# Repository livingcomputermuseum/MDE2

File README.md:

# MDE2 - MASSBUS Disk Emulator

This repository contains the Xilinx VHDL code and PCB designs for the MASSBUS Disk Emulator.

This is used in tandem with the MBS server code to emulate MASSBUS peripherals.

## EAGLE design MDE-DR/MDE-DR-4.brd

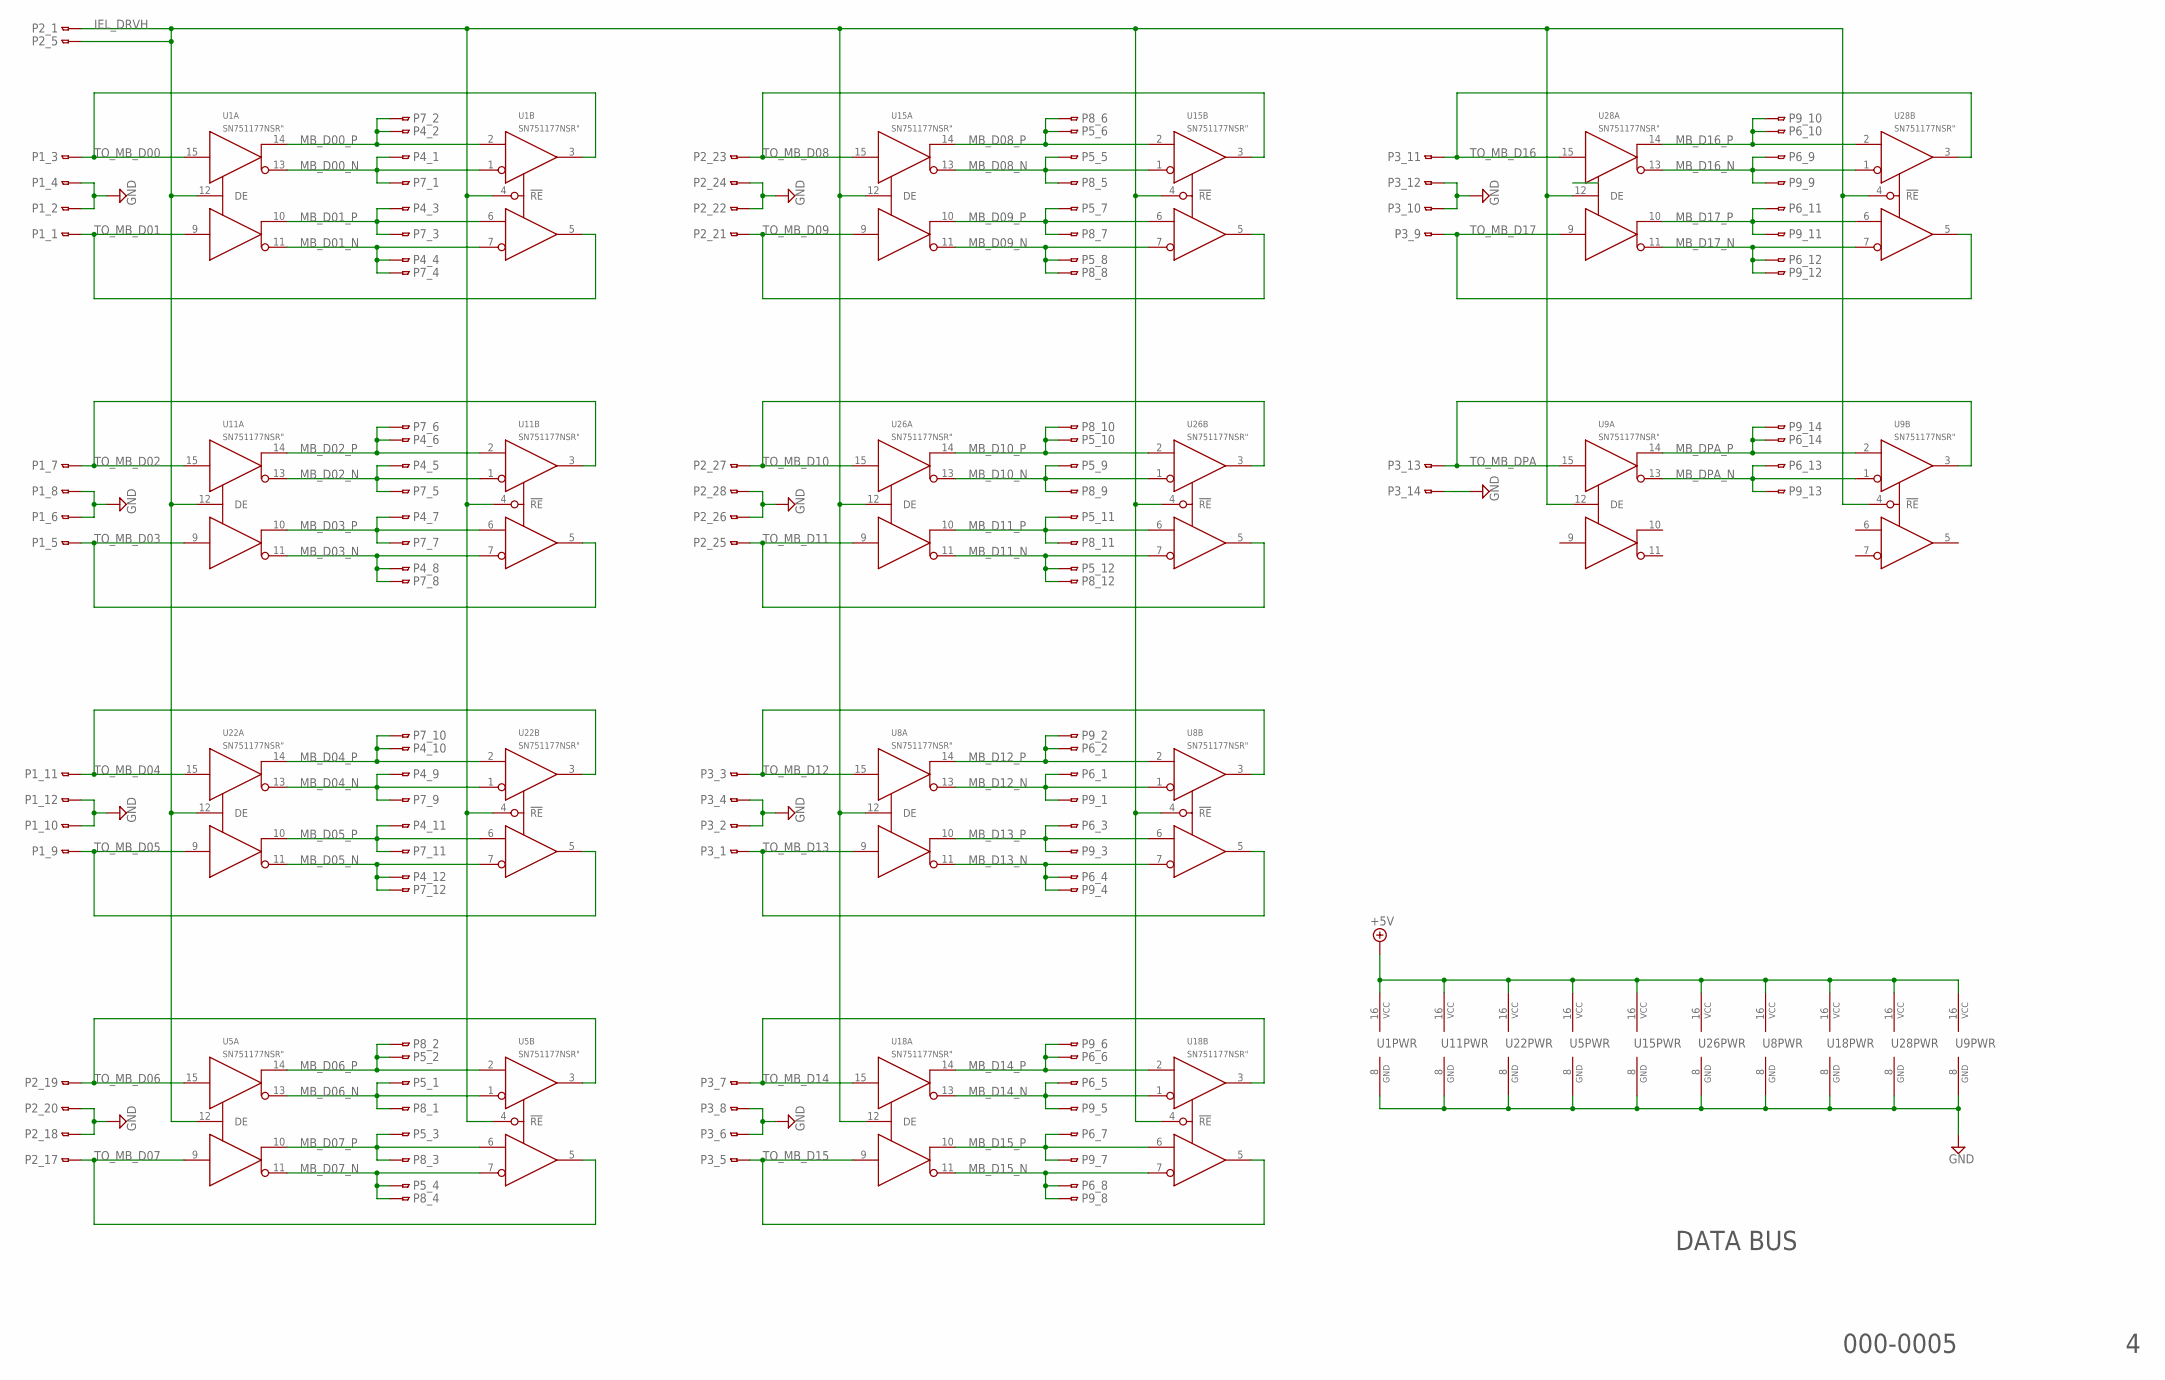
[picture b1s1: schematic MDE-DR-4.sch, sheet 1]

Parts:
P1, P2, P3: CON50L
P4, P5, P6, P7, P8, P9: CON40L
U1, U5, U8, U9, U11, U15, U18, U22, U26, U28: SN751177NSR"; SO16NS

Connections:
+5V: U1.16 (VCC), U5.16 (VCC), U8.16 (VCC), U9.16 (VCC), U11.16 (VCC), U15.16 (VCC), U18.16 (VCC), U22.16 (VCC), U26.16 (VCC), U28.16 (VCC); also elsewhere on the board
GND: P1.2, P1.4, P1.6, P1.8, P1.10, P1.12, P2.18, P2.20, P2.22, P2.24, P2.26, P2.28, P3.2, P3.4, P3.6, P3.8, P3.10, P3.12, P3.14, U1.8 (GND), U5.8 (GND), U8.8 (GND), U9.8 (GND), U11.8 (GND), U15.8 (GND), U18.8 (GND), U22.8 (GND), U26.8 (GND), U28.8 (GND); also elsewhere on the board
IEL_DRVH: P2.1, P2.5, U1.4 (!RE), U1.12 (DE), U5.4 (!RE), U5.12 (DE), U8.4 (!RE), U8.12 (DE), U9.4 (!RE), U9.12 (DE), U11.4 (!RE), U11.12 (DE), U15.4 (!RE), U15.12 (DE), U18.4 (!RE), U18.12 (DE), U22.4 (!RE), U22.12 (DE), U26.4 (!RE), U26.12 (DE), U28.4 (!RE), U28.12 (DE)
MB_D00_N: P4.1, P7.1, U1.1 (!1B), U1.13 (!1Z)
MB_D00_P: P4.2, P7.2, U1.2 (1A), U1.14 (1Y)
MB_D01_N: P4.4, P7.4, U1.7 (!2B), U1.11 (!2Z)
MB_D01_P: P4.3, P7.3, U1.6 (2A), U1.10 (2Y)
MB_D02_N: P4.5, P7.5, U11.1 (!1B), U11.13 (!1Z)
MB_D02_P: P4.6, P7.6, U11.2 (1A), U11.14 (1Y)
MB_D03_N: P4.8, P7.8, U11.7 (!2B), U11.11 (!2Z)
MB_D03_P: P4.7, P7.7, U11.6 (2A), U11.10 (2Y)
MB_D04_N: P4.9, P7.9, U22.1 (!1B), U22.13 (!1Z)
MB_D04_P: P4.10, P7.10, U22.2 (1A), U22.14 (1Y)
MB_D05_N: P4.12, P7.12, U22.7 (!2B), U22.11 (!2Z)
MB_D05_P: P4.11, P7.11, U22.6 (2A), U22.10 (2Y)
MB_D06_N: P5.1, P8.1, U5.1 (!1B), U5.13 (!1Z)
MB_D06_P: P5.2, P8.2, U5.2 (1A), U5.14 (1Y)
MB_D07_N: P5.4, P8.4, U5.7 (!2B), U5.11 (!2Z)
MB_D07_P: P5.3, P8.3, U5.6 (2A), U5.10 (2Y)
MB_D08_N: P5.5, P8.5, U15.1 (!1B), U15.13 (!1Z)
MB_D08_P: P5.6, P8.6, U15.2 (1A), U15.14 (1Y)
MB_D09_N: P5.8, P8.8, U15.7 (!2B), U15.11 (!2Z)
MB_D09_P: P5.7, P8.7, U15.6 (2A), U15.10 (2Y)
MB_D10_N: P5.9, P8.9, U26.1 (!1B), U26.13 (!1Z)
MB_D10_P: P5.10, P8.10, U26.2 (1A), U26.14 (1Y)
MB_D11_N: P5.12, P8.12, U26.7 (!2B), U26.11 (!2Z)
MB_D11_P: P5.11, P8.11, U26.6 (2A), U26.10 (2Y)
MB_D12_N: P6.1, P9.1, U8.1 (!1B), U8.13 (!1Z)
MB_D12_P: P6.2, P9.2, U8.2 (1A), U8.14 (1Y)
MB_D13_N: P6.4, P9.4, U8.7 (!2B), U8.11 (!2Z)
MB_D13_P: P6.3, P9.3, U8.6 (2A), U8.10 (2Y)
MB_D14_N: P6.5, P9.5, U18.1 (!1B), U18.13 (!1Z)
MB_D14_P: P6.6, P9.6, U18.2 (1A), U18.14 (1Y)
MB_D15_N: P6.8, P9.8, U18.7 (!2B), U18.11 (!2Z)
MB_D15_P: P6.7, P9.7, U18.6 (2A), U18.10 (2Y)
MB_D16_N: P6.9, P9.9, U28.1 (!1B), U28.13 (!1Z)
MB_D16_P: P6.10, P9.10, U28.2 (1A), U28.14 (1Y)
MB_D17_N: P6.12, P9.12, U28.7 (!2B), U28.11 (!2Z)
MB_D17_P: P6.11, P9.11, U28.6 (2A), U28.10 (2Y)
MB_DPA_N: P6.13, P9.13, U9.1 (!1B), U9.13 (!1Z)
MB_DPA_P: P6.14, P9.14, U9.2 (1A), U9.14 (1Y)
TO_MB_D00: P1.3, U1.3 (1R), U1.15 (1D)
TO_MB_D01: P1.1, U1.5 (2R), U1.9 (2D)
TO_MB_D02: P1.7, U11.3 (1R), U11.15 (1D)
TO_MB_D03: P1.5, U11.5 (2R), U11.9 (2D)
TO_MB_D04: P1.11, U22.3 (1R), U22.15 (1D)
TO_MB_D05: P1.9, U22.5 (2R), U22.9 (2D)
TO_MB_D06: P2.19, U5.3 (1R), U5.15 (1D)
TO_MB_D07: P2.17, U5.5 (2R), U5.9 (2D)
TO_MB_D08: P2.23, U15.3 (1R), U15.15 (1D)
TO_MB_D09: P2.21, U15.5 (2R), U15.9 (2D)
TO_MB_D10: P2.27, U26.3 (1R), U26.15 (1D)
TO_MB_D11: P2.25, U26.5 (2R), U26.9 (2D)
TO_MB_D12: P3.3, U8.3 (1R), U8.15 (1D)
TO_MB_D13: P3.1, U8.5 (2R), U8.9 (2D)
TO_MB_D14: P3.7, U18.3 (1R), U18.15 (1D)
TO_MB_D15: P3.5, U18.5 (2R), U18.9 (2D)
TO_MB_D16: P3.11, U28.3 (1R), U28.15 (1D)
TO_MB_D17: P3.9, U28.5 (2R), U28.9 (2D)
TO_MB_DPA: P3.13, U9.3 (1R), U9.15 (1D)

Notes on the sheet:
DATA BUS
000-0005

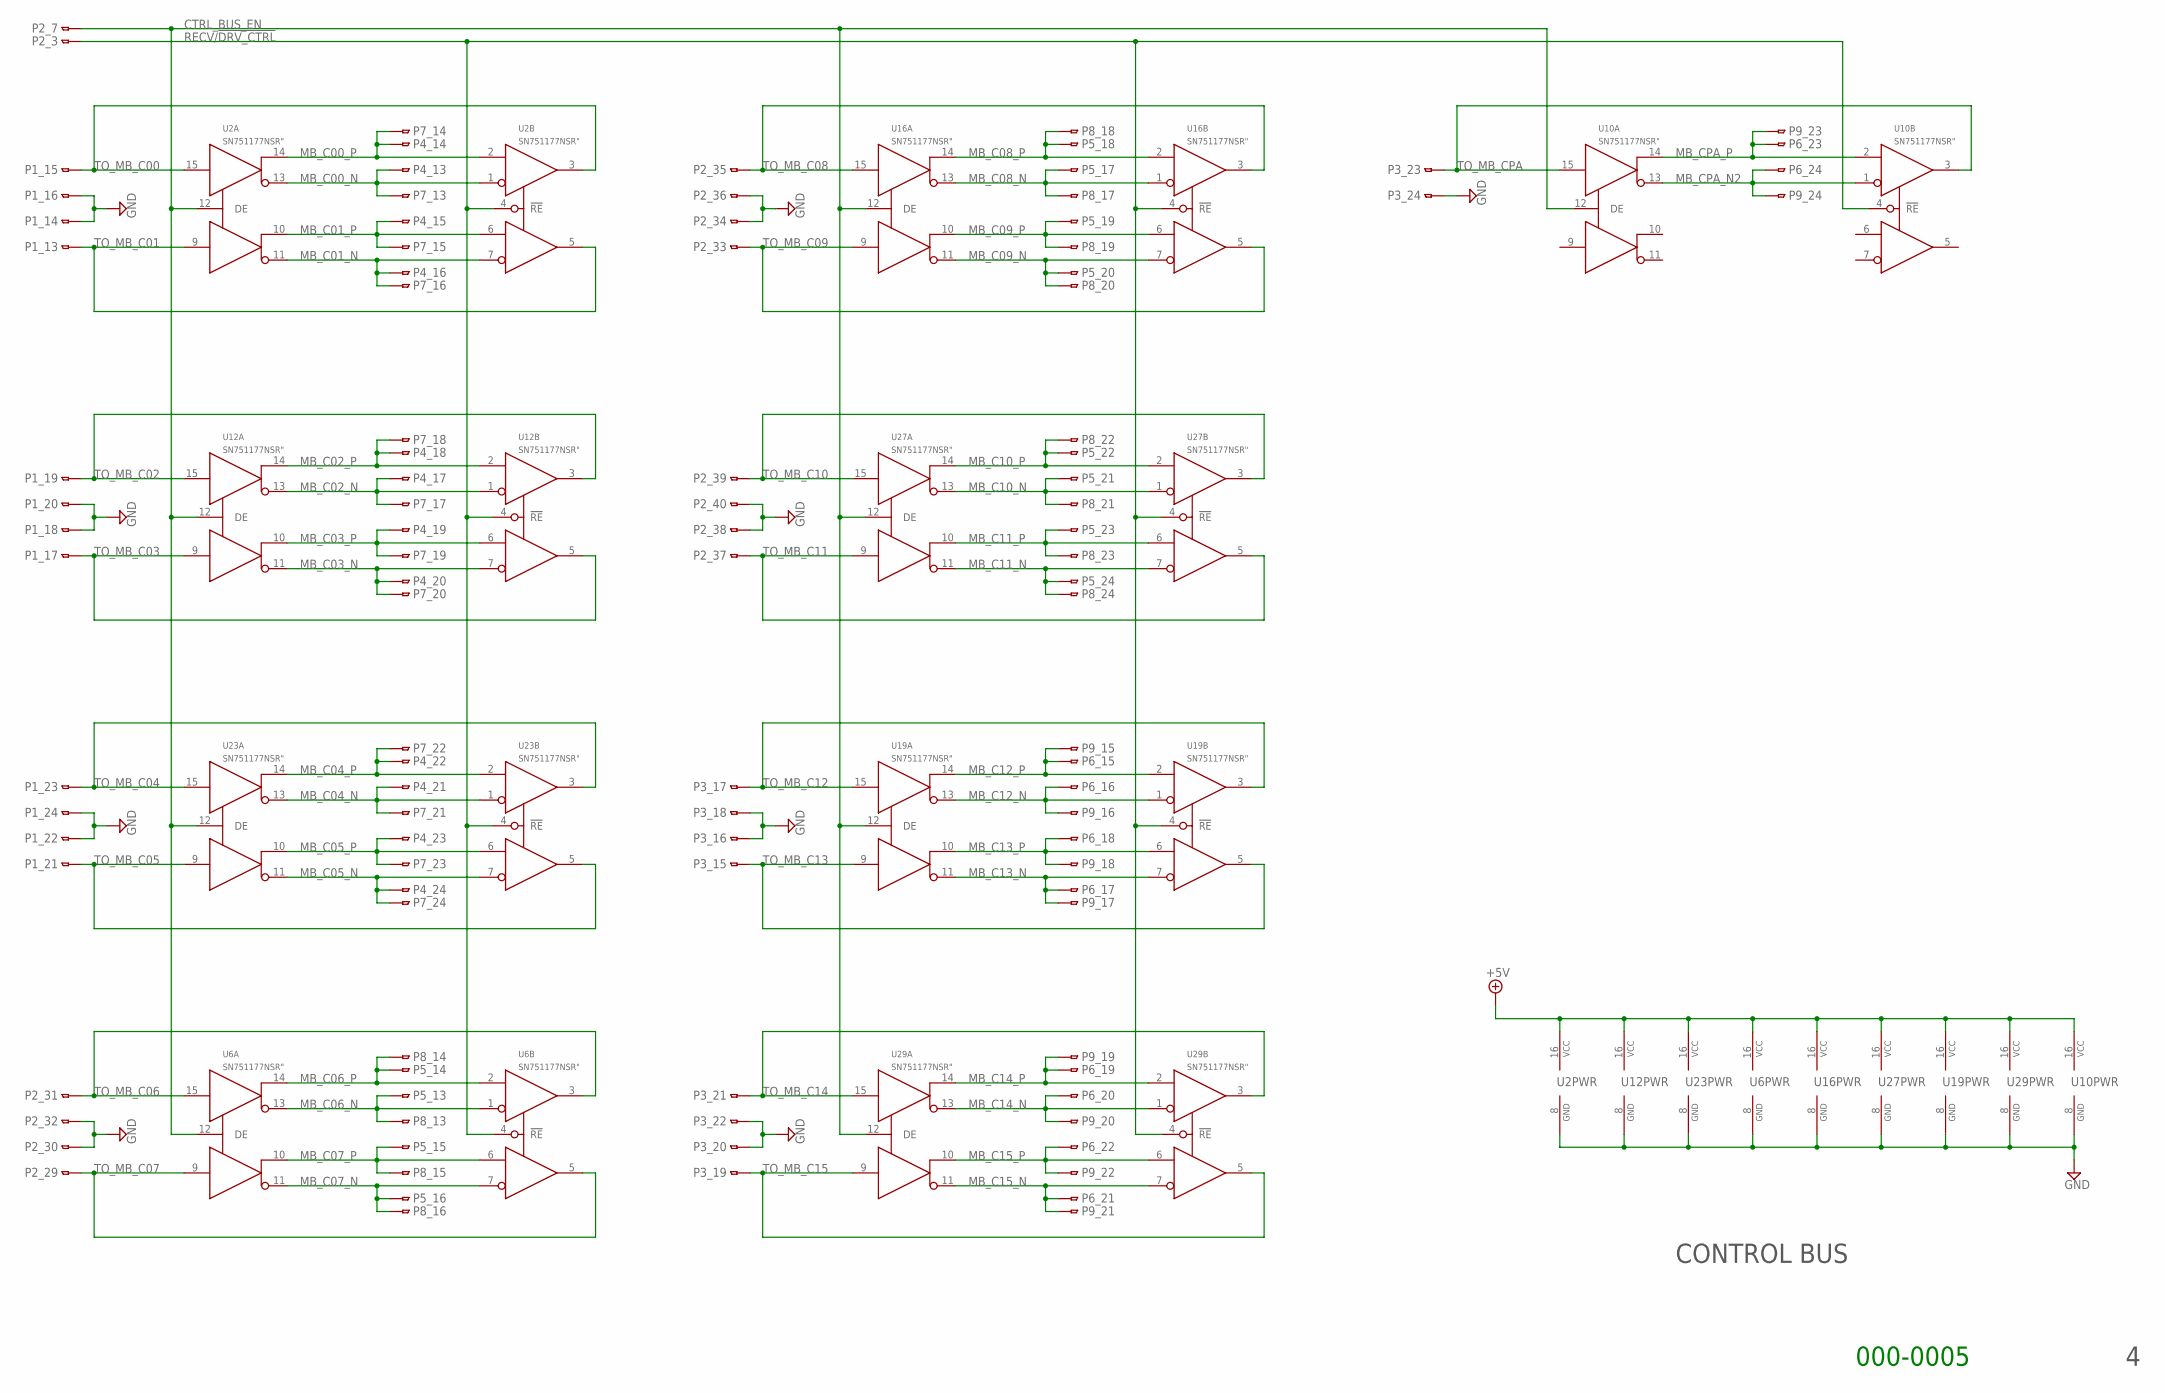
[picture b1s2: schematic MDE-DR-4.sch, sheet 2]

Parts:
P1, P2, P3: CON50L
P4, P5, P6, P7, P8, P9: CON40L
U2, U6, U10, U12, U16, U19, U23, U27, U29: SN751177NSR"; SO16NS

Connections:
+5V: U2.16 (VCC), U6.16 (VCC), U10.16 (VCC), U12.16 (VCC), U16.16 (VCC), U19.16 (VCC), U23.16 (VCC), U27.16 (VCC), U29.16 (VCC); also elsewhere on the board
CTRL_BUS_EN: P2.7, U2.12 (DE), U6.12 (DE), U10.12 (DE), U12.12 (DE), U16.12 (DE), U19.12 (DE), U23.12 (DE), U27.12 (DE), U29.12 (DE)
GND: P1.14, P1.16, P1.18, P1.20, P1.22, P1.24, P2.30, P2.32, P2.34, P2.36, P2.38, P2.40, P3.16, P3.18, P3.20, P3.22, P3.24, U2.8 (GND), U6.8 (GND), U10.8 (GND), U12.8 (GND), U16.8 (GND), U19.8 (GND), U23.8 (GND), U27.8 (GND), U29.8 (GND); also elsewhere on the board
MB_C00_N: P4.13, P7.13, U2.1 (!1B), U2.13 (!1Z)
MB_C00_P: P4.14, P7.14, U2.2 (1A), U2.14 (1Y)
MB_C01_N: P4.16, P7.16, U2.7 (!2B), U2.11 (!2Z)
MB_C01_P: P4.15, P7.15, U2.6 (2A), U2.10 (2Y)
MB_C02_N: P4.17, P7.17, U12.1 (!1B), U12.13 (!1Z)
MB_C02_P: P4.18, P7.18, U12.2 (1A), U12.14 (1Y)
MB_C03_N: P4.20, P7.20, U12.7 (!2B), U12.11 (!2Z)
MB_C03_P: P4.19, P7.19, U12.6 (2A), U12.10 (2Y)
MB_C04_N: P4.21, P7.21, U23.1 (!1B), U23.13 (!1Z)
MB_C04_P: P4.22, P7.22, U23.2 (1A), U23.14 (1Y)
MB_C05_N: P4.24, P7.24, U23.7 (!2B), U23.11 (!2Z)
MB_C05_P: P4.23, P7.23, U23.6 (2A), U23.10 (2Y)
MB_C06_N: P5.13, P8.13, U6.1 (!1B), U6.13 (!1Z)
MB_C06_P: P5.14, P8.14, U6.2 (1A), U6.14 (1Y)
MB_C07_N: P5.16, P8.16, U6.7 (!2B), U6.11 (!2Z)
MB_C07_P: P5.15, P8.15, U6.6 (2A), U6.10 (2Y)
MB_C08_N: P5.17, P8.17, U16.1 (!1B), U16.13 (!1Z)
MB_C08_P: P5.18, P8.18, U16.2 (1A), U16.14 (1Y)
MB_C09_N: P5.20, P8.20, U16.7 (!2B), U16.11 (!2Z)
MB_C09_P: P5.19, P8.19, U16.6 (2A), U16.10 (2Y)
MB_C10_N: P5.21, P8.21, U27.1 (!1B), U27.13 (!1Z)
MB_C10_P: P5.22, P8.22, U27.2 (1A), U27.14 (1Y)
MB_C11_N: P5.24, P8.24, U27.7 (!2B), U27.11 (!2Z)
MB_C11_P: P5.23, P8.23, U27.6 (2A), U27.10 (2Y)
MB_C12_N: P6.16, P9.16, U19.1 (!1B), U19.13 (!1Z)
MB_C12_P: P6.15, P9.15, U19.2 (1A), U19.14 (1Y)
MB_C13_N: P6.17, P9.17, U19.7 (!2B), U19.11 (!2Z)
MB_C13_P: P6.18, P9.18, U19.6 (2A), U19.10 (2Y)
MB_C14_N: P6.20, P9.20, U29.1 (!1B), U29.13 (!1Z)
MB_C14_P: P6.19, P9.19, U29.2 (1A), U29.14 (1Y)
MB_C15_N: P6.21, P9.21, U29.7 (!2B), U29.11 (!2Z)
MB_C15_P: P6.22, P9.22, U29.6 (2A), U29.10 (2Y)
MB_CPA_N2: P6.24, P9.24, U10.1 (!1B), U10.13 (!1Z)
MB_CPA_P: P6.23, P9.23, U10.2 (1A), U10.14 (1Y)
RECV/!DRV_CTRL: P2.3, U2.4 (!RE), U6.4 (!RE), U10.4 (!RE), U12.4 (!RE), U16.4 (!RE), U19.4 (!RE), U23.4 (!RE), U27.4 (!RE), U29.4 (!RE)
TO_MB_C00: P1.15, U2.3 (1R), U2.15 (1D)
TO_MB_C01: P1.13, U2.5 (2R), U2.9 (2D)
TO_MB_C02: P1.19, U12.3 (1R), U12.15 (1D)
TO_MB_C03: P1.17, U12.5 (2R), U12.9 (2D)
TO_MB_C04: P1.23, U23.3 (1R), U23.15 (1D)
TO_MB_C05: P1.21, U23.5 (2R), U23.9 (2D)
TO_MB_C06: P2.31, U6.3 (1R), U6.15 (1D)
TO_MB_C07: P2.29, U6.5 (2R), U6.9 (2D)
TO_MB_C08: P2.35, U16.3 (1R), U16.15 (1D)
TO_MB_C09: P2.33, U16.5 (2R), U16.9 (2D)
TO_MB_C10: P2.39, U27.3 (1R), U27.15 (1D)
TO_MB_C11: P2.37, U27.5 (2R), U27.9 (2D)
TO_MB_C12: P3.17, U19.3 (1R), U19.15 (1D)
TO_MB_C13: P3.15, U19.5 (2R), U19.9 (2D)
TO_MB_C14: P3.21, U29.3 (1R), U29.15 (1D)
TO_MB_C15: P3.19, U29.5 (2R), U29.9 (2D)
TO_MB_CPA: P3.23, U10.3 (1R), U10.15 (1D)

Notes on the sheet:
CONTROL BUS
000-0005

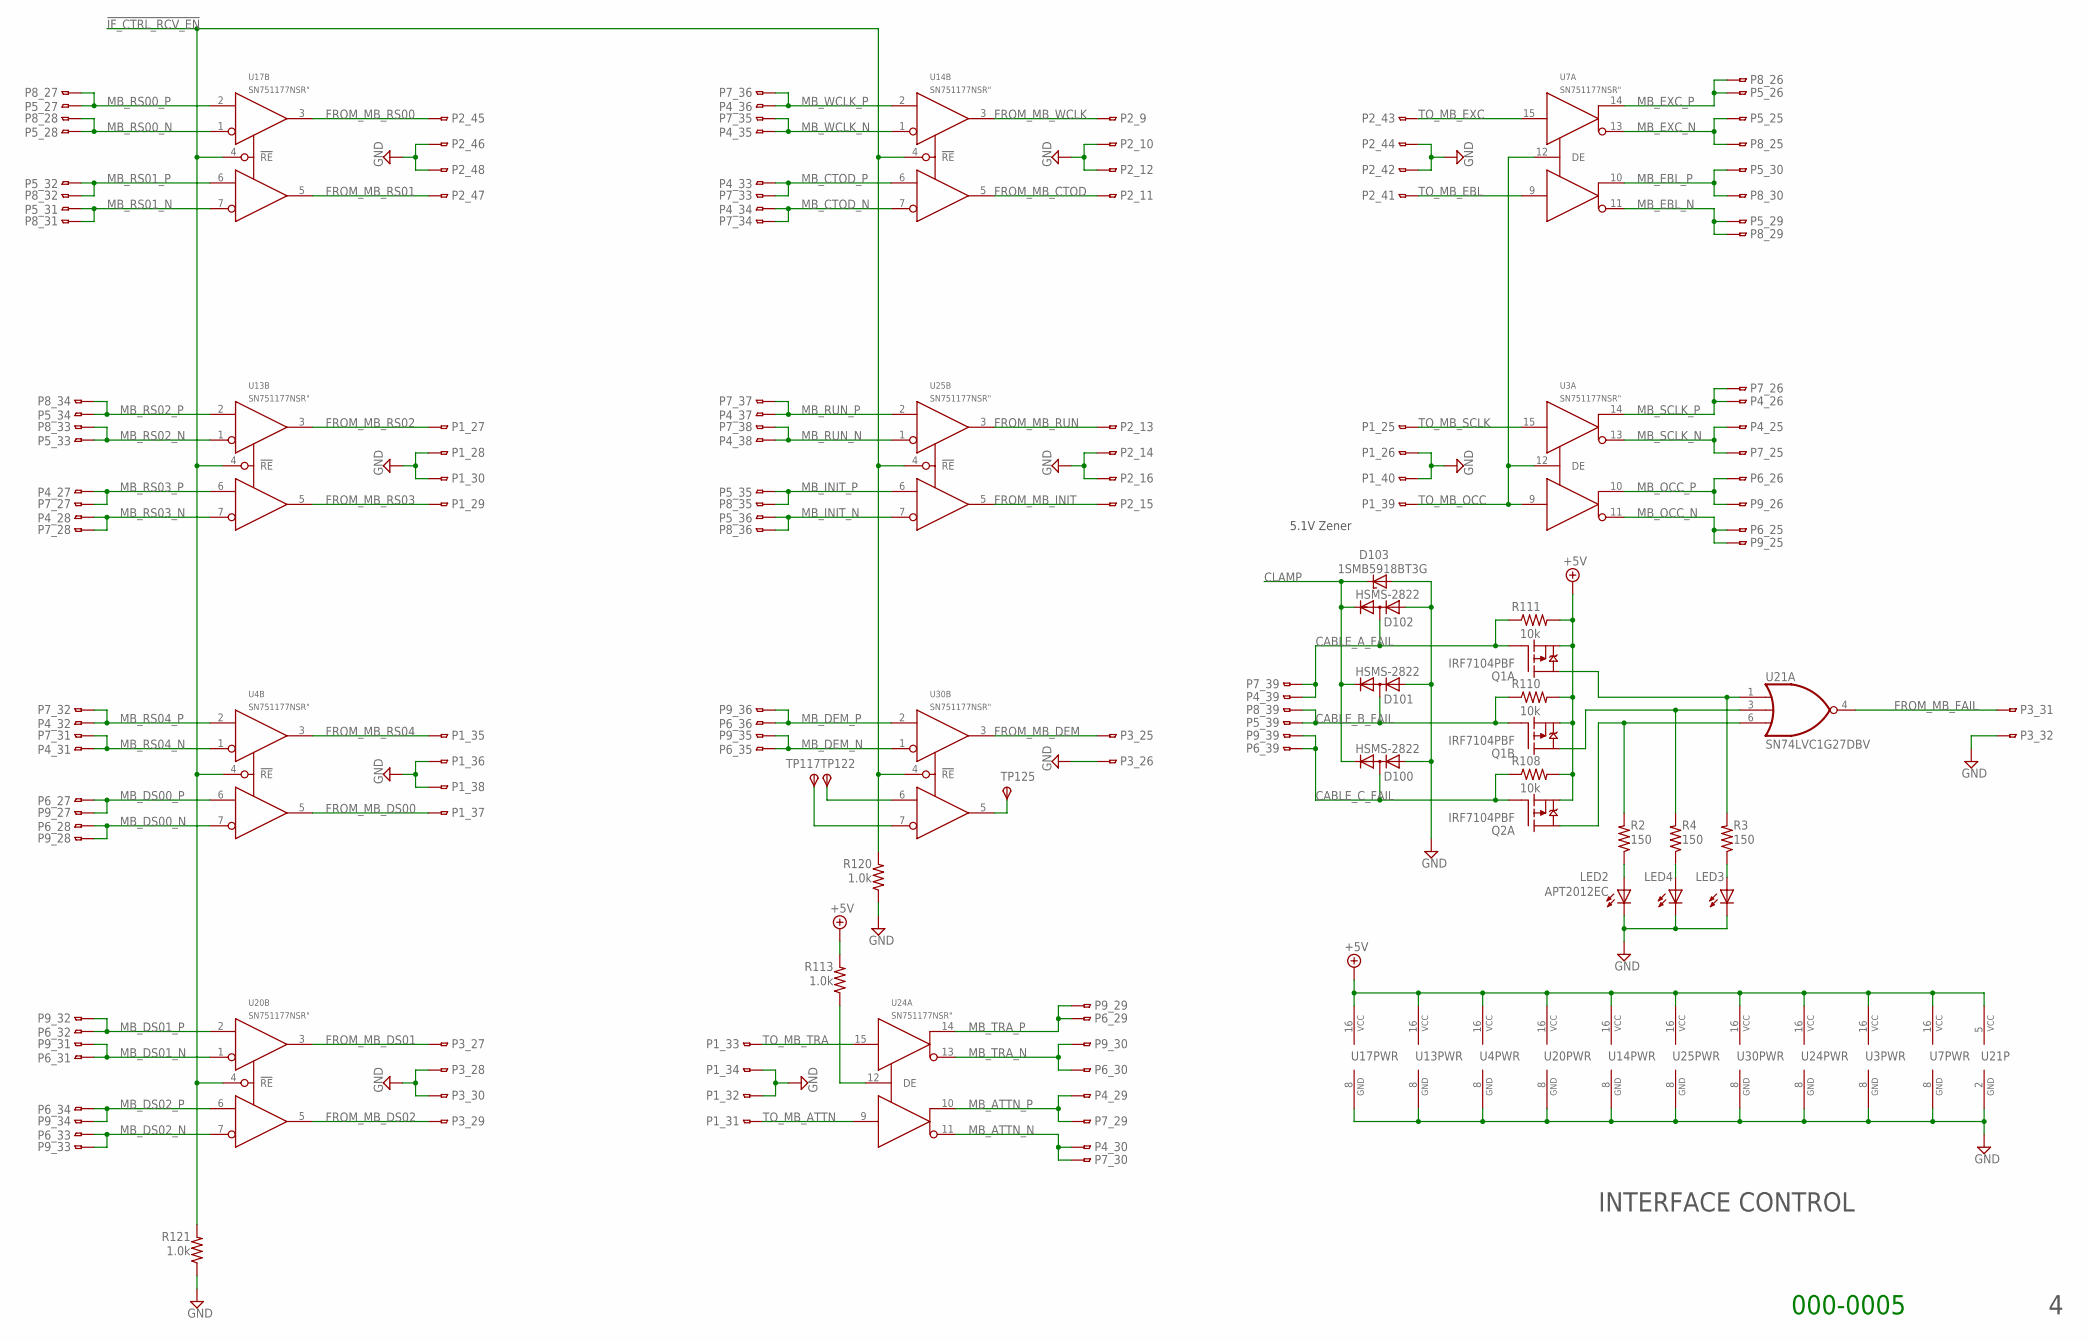
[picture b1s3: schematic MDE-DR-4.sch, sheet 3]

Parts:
D100, D101, D102: HSMS-2822; SOT23
D103: 1SMB5918BT3G; SMB
LED2, LED3, LED4: APT2012EC; SML0805
P1, P2, P3: CON50L
P4, P5, P6, P7, P8, P9: CON40L
Q1, Q2: IRF7104PBF; SO-08
R2, R3, R4: 150; R0805
R108, R110, R111: 10k; R0805
R113, R120, R121: 1.0k; R0805
TP117, TP122, TP125: TPSTP12R; TP12R
U3, U4, U7, U13, U14, U17, U20, U24, U25, U30: SN751177NSR"; SO16NS
U21: SN74LVC1G27DBV; DBV_R-PDSO-G6

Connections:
!IF_CTRL_RCV_EN: R120.2, R121.2, U4.4 (!RE), U13.4 (!RE), U14.4 (!RE), U17.4 (!RE), U20.4 (!RE), U25.4 (!RE), U30.4 (!RE)
+5V: Q1.1 (S), Q1.3 (S), Q2.1 (S), R108.2, R110.2, R111.2, R113.2, U3.16 (VCC), U4.16 (VCC), U7.16 (VCC), U13.16 (VCC), U14.16 (VCC), U17.16 (VCC), U20.16 (VCC), U21.5 (VCC), U24.16 (VCC), U25.16 (VCC), U30.16 (VCC); also elsewhere on the board
CABLE_A_FAIL: D102.3 (AC), P4.39, P7.39, Q1.2 (G), R111.1
CABLE_B_FAIL: D101.3 (AC), P5.39, P8.39, Q1.4 (G), R110.1
CABLE_C_FAIL: D100.3 (AC), P6.39, P9.39, Q2.2 (G), R108.1
CLAMP: D100.2 (C), D101.2 (C), D102.2 (C), D103.C
FROM_MB_CTOD: P2.11, U14.5 (2R)
FROM_MB_DEM: P3.25, U30.3 (1R)
FROM_MB_DS00: P1.37, U4.5 (2R)
FROM_MB_DS01: P3.27, U20.3 (1R)
FROM_MB_DS02: P3.29, U20.5 (2R)
FROM_MB_FAIL: P3.31, U21.4 (Y)
FROM_MB_INIT: P2.15, U25.5 (2R)
FROM_MB_RS00: P2.45, U17.3 (1R)
FROM_MB_RS01: P2.47, U17.5 (2R)
FROM_MB_RS02: P1.27, U13.3 (1R)
FROM_MB_RS03: P1.29, U13.5 (2R)
FROM_MB_RS04: P1.35, U4.3 (1R)
FROM_MB_RUN: P2.13, U25.3 (1R)
FROM_MB_WCLK: P2.9, U14.3 (1R)
GND: D100.1 (A), D101.1 (A), D102.1 (A), D103.A, LED2.C, LED3.C, LED4.C, P1.26, P1.28, P1.30, P1.32, P1.34, P1.36, P1.38, P1.40, P2.10, P2.12, P2.14, P2.16, P2.42, P2.44, P2.46, P2.48, P3.26, P3.28, P3.30, P3.32, R120.1, R121.1, U3.8 (GND), U4.8 (GND), U7.8 (GND), U13.8 (GND), U14.8 (GND), U17.8 (GND), U20.8 (GND), U21.2 (GND), U24.8 (GND), U25.8 (GND), U30.8 (GND); also elsewhere on the board
MB_ATTN_N: P4.30, P7.30, U24.11 (!2Z)
MB_ATTN_P: P4.29, P7.29, U24.10 (2Y)
MB_CTOD_N: P4.34, P7.34, U14.7 (!2B)
MB_CTOD_P: P4.33, P7.33, U14.6 (2A)
MB_DEM_N: P6.35, P9.35, U30.1 (!1B)
MB_DEM_P: P6.36, P9.36, U30.2 (1A)
MB_DS00_N: P6.28, P9.28, U4.7 (!2B)
MB_DS00_P: P6.27, P9.27, U4.6 (2A)
MB_DS01_N: P6.31, P9.31, U20.1 (!1B)
MB_DS01_P: P6.32, P9.32, U20.2 (1A)
MB_DS02_N: P6.33, P9.33, U20.7 (!2B)
MB_DS02_P: P6.34, P9.34, U20.6 (2A)
MB_EBL_N: P5.29, P8.29, U7.11 (!2Z)
MB_EBL_P: P5.30, P8.30, U7.10 (2Y)
MB_EXC_N: P5.25, P8.25, U7.13 (!1Z)
MB_EXC_P: P5.26, P8.26, U7.14 (1Y)
MB_INIT_N: P5.36, P8.36, U25.7 (!2B)
MB_INIT_P: P5.35, P8.35, U25.6 (2A)
MB_OCC_N: P6.25, P9.25, U3.11 (!2Z)
MB_OCC_P: P6.26, P9.26, U3.10 (2Y)
MB_RS00_N: P5.28, P8.28, U17.1 (!1B)
MB_RS00_P: P5.27, P8.27, U17.2 (1A)
MB_RS01_N: P5.31, P8.31, U17.7 (!2B)
MB_RS01_P: P5.32, P8.32, U17.6 (2A)
MB_RS02_N: P5.33, P8.33, U13.1 (!1B)
MB_RS02_P: P5.34, P8.34, U13.2 (1A)
MB_RS03_N: P4.28, P7.28, U13.7 (!2B)
MB_RS03_P: P4.27, P7.27, U13.6 (2A)
MB_RS04_N: P4.31, P7.31, U4.1 (!1B)
MB_RS04_P: P4.32, P7.32, U4.2 (1A)
MB_RUN_N: P4.38, P7.38, U25.1 (!1B)
MB_RUN_P: P4.37, P7.37, U25.2 (1A)
MB_SCLK_N: P4.25, P7.25, U3.13 (!1Z)
MB_SCLK_P: P4.26, P7.26, U3.14 (1Y)
MB_TRA_N: P6.30, P9.30, U24.13 (!1Z)
MB_TRA_P: P6.29, P9.29, U24.14 (1Y)
MB_WCLK_N: P4.35, P7.35, U14.1 (!1B)
MB_WCLK_P: P4.36, P7.36, U14.2 (1A)
unnamed: R113.1, U24.12 (DE)
unnamed: TP117.TP, U30.7 (!2B)
unnamed: LED2.A, R2.1
unnamed: Q2.7 (D), Q2.8 (D), R2.2, U21.6 (C)
unnamed: Q1.5 (D), Q1.6 (D), R4.2, U21.3 (B)
unnamed: Q1.7 (D), Q1.8 (D), R3.2, U21.1 (A)
unnamed: LED4.A, R4.1
unnamed: LED3.A, R3.1
unnamed: TP125.TP, U30.5 (2R)
unnamed: TP122.TP, U30.6 (2A)
TO_MB_ATTN: P1.31, U24.9 (2D)
TO_MB_EBL: P2.41, U7.9 (2D)
TO_MB_EXC: P2.43, U7.15 (1D)
TO_MB_OCC: P1.39, U3.9 (2D), U3.12 (DE), U7.12 (DE)
TO_MB_SCLK: P1.25, U3.15 (1D)
TO_MB_TRA: P1.33, U24.15 (1D)

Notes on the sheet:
INTERFACE CONTROL
5.1V Zener
000-0005
